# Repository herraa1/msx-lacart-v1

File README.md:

# MSX LOGICAL ANALYZER CART

This is a MSX cartridge to facilitate the use of a Logical Analyzer with MSX cartridges and slot signals.

It uses [Agustín Gimenez Bernad](https://github.com/gusmanb) Raspberry Pico 2 based [logicanalizer](https://github.com/gusmanb/logicanalyzer) as a companion card.

## Current Status

* First prototype PCB sent for manufacturing as of Apr 3rd 2026.
* First prototype PCB tested successfully as of Apr 18th 2026.

> [!NOTE]
> Documentation in progress

## [Hardware](hardware/kicad/)

The msx-lacart is made of a 4-layer PCB with minimal components.

### [msx-lacart-v1-build1](hardware/kicad/msx-lacart-v1-build1/)

:white_check_mark: This board has been successfully built and tested.

[Bill Of Materials (BoM)](https://htmlpreview.github.io/?https://raw.githubusercontent.com/herraa1/msx-lacart-v1/main/hardware/kicad/msx-lacart-v1-build1/bom/ibom.html)

[Schematic and PCB](https://kicanvas.org/?github=https%3A%2F%2Fgithub.com%2Fherraa1%2Fmsx-lacart-v1%2Ftree%2Fmain%2Fhardware%2Fkicad%2Fmsx-lacart-v1-build1)

|||
|-|-|
|msx-lacart-v1 build1<br>PCB unpopulated front|msx-lacart-v1 build1<br>PCB unpopulated back|

||
|:--|
|msx-lacart-v1 build1 PCB populated front|

||
|:--|
|msx-lacart-v1 build1 PCB populated back|

## Usage

||
|:--|
|msx-lacart-v1 inserted into slot1 of a MSX JFF inspecting a Knighmare cartridge|

||
|:--|
|msx-lacart-v1 with Logic Analyzer capture session|

```
                    di                                      ;[0000] f3
                    jp        $02d7                         ;[0001] c3 d7 02
[...]
                    ld        a,$82                         ;[02d7] 3e 82
                    out       ($ab),a                       ;[02d9] d3 ab
                    xor       a                             ;[02db] af
                    out       ($a8),a                       ;[02dc] d3 a8
                    ld        a,$50                         ;[02de] 3e 50
                    out       ($aa),a                       ;[02e0] d3 aa
                    ld        de,$ffff                      ;[02e2] 11 ff ff
                    xor       a                             ;[02e5] af
                    ld        c,a                           ;[02e6] 4f
                    out       ($a8),a                       ;[02e7] d3 a8
                    sla       c                             ;[02e9] cb 21
                    ld        b,$00                         ;[02eb] 06 00
                    ld        hl,$ffff                      ;[02ed] 21 ff ff
                    ld        (hl),$f0                      ;[02f0] 36 f0
                    ld        a,(hl)                        ;[02f2] 7e
                    sub       $0f                           ;[02f3] d6 0f
                    jr        nz,$0302                      ;[02f5] 20 0b
[...]
                    ld        hl,$bf00                      ;[0302] 21 00 bf
                    ld        a,(hl)                        ;[0305] 7e
                    cpl                                     ;[0306] 2f
                    ld        (hl),a                        ;[0307] 77
```
||
|:--|
|Original MSX BIOS Z80 instructions from BIOS disassembly|

||
|:--|
|El Dr Gusman Logic Analyzer 6.5 showing MSX BIOS Z80 boot instructions captured using msx-lacart-v1|

||
|:--|
|PulseView loaded with CSV export of MSX BIOS Z80 boot instructions captured using msx-lacart-v1|

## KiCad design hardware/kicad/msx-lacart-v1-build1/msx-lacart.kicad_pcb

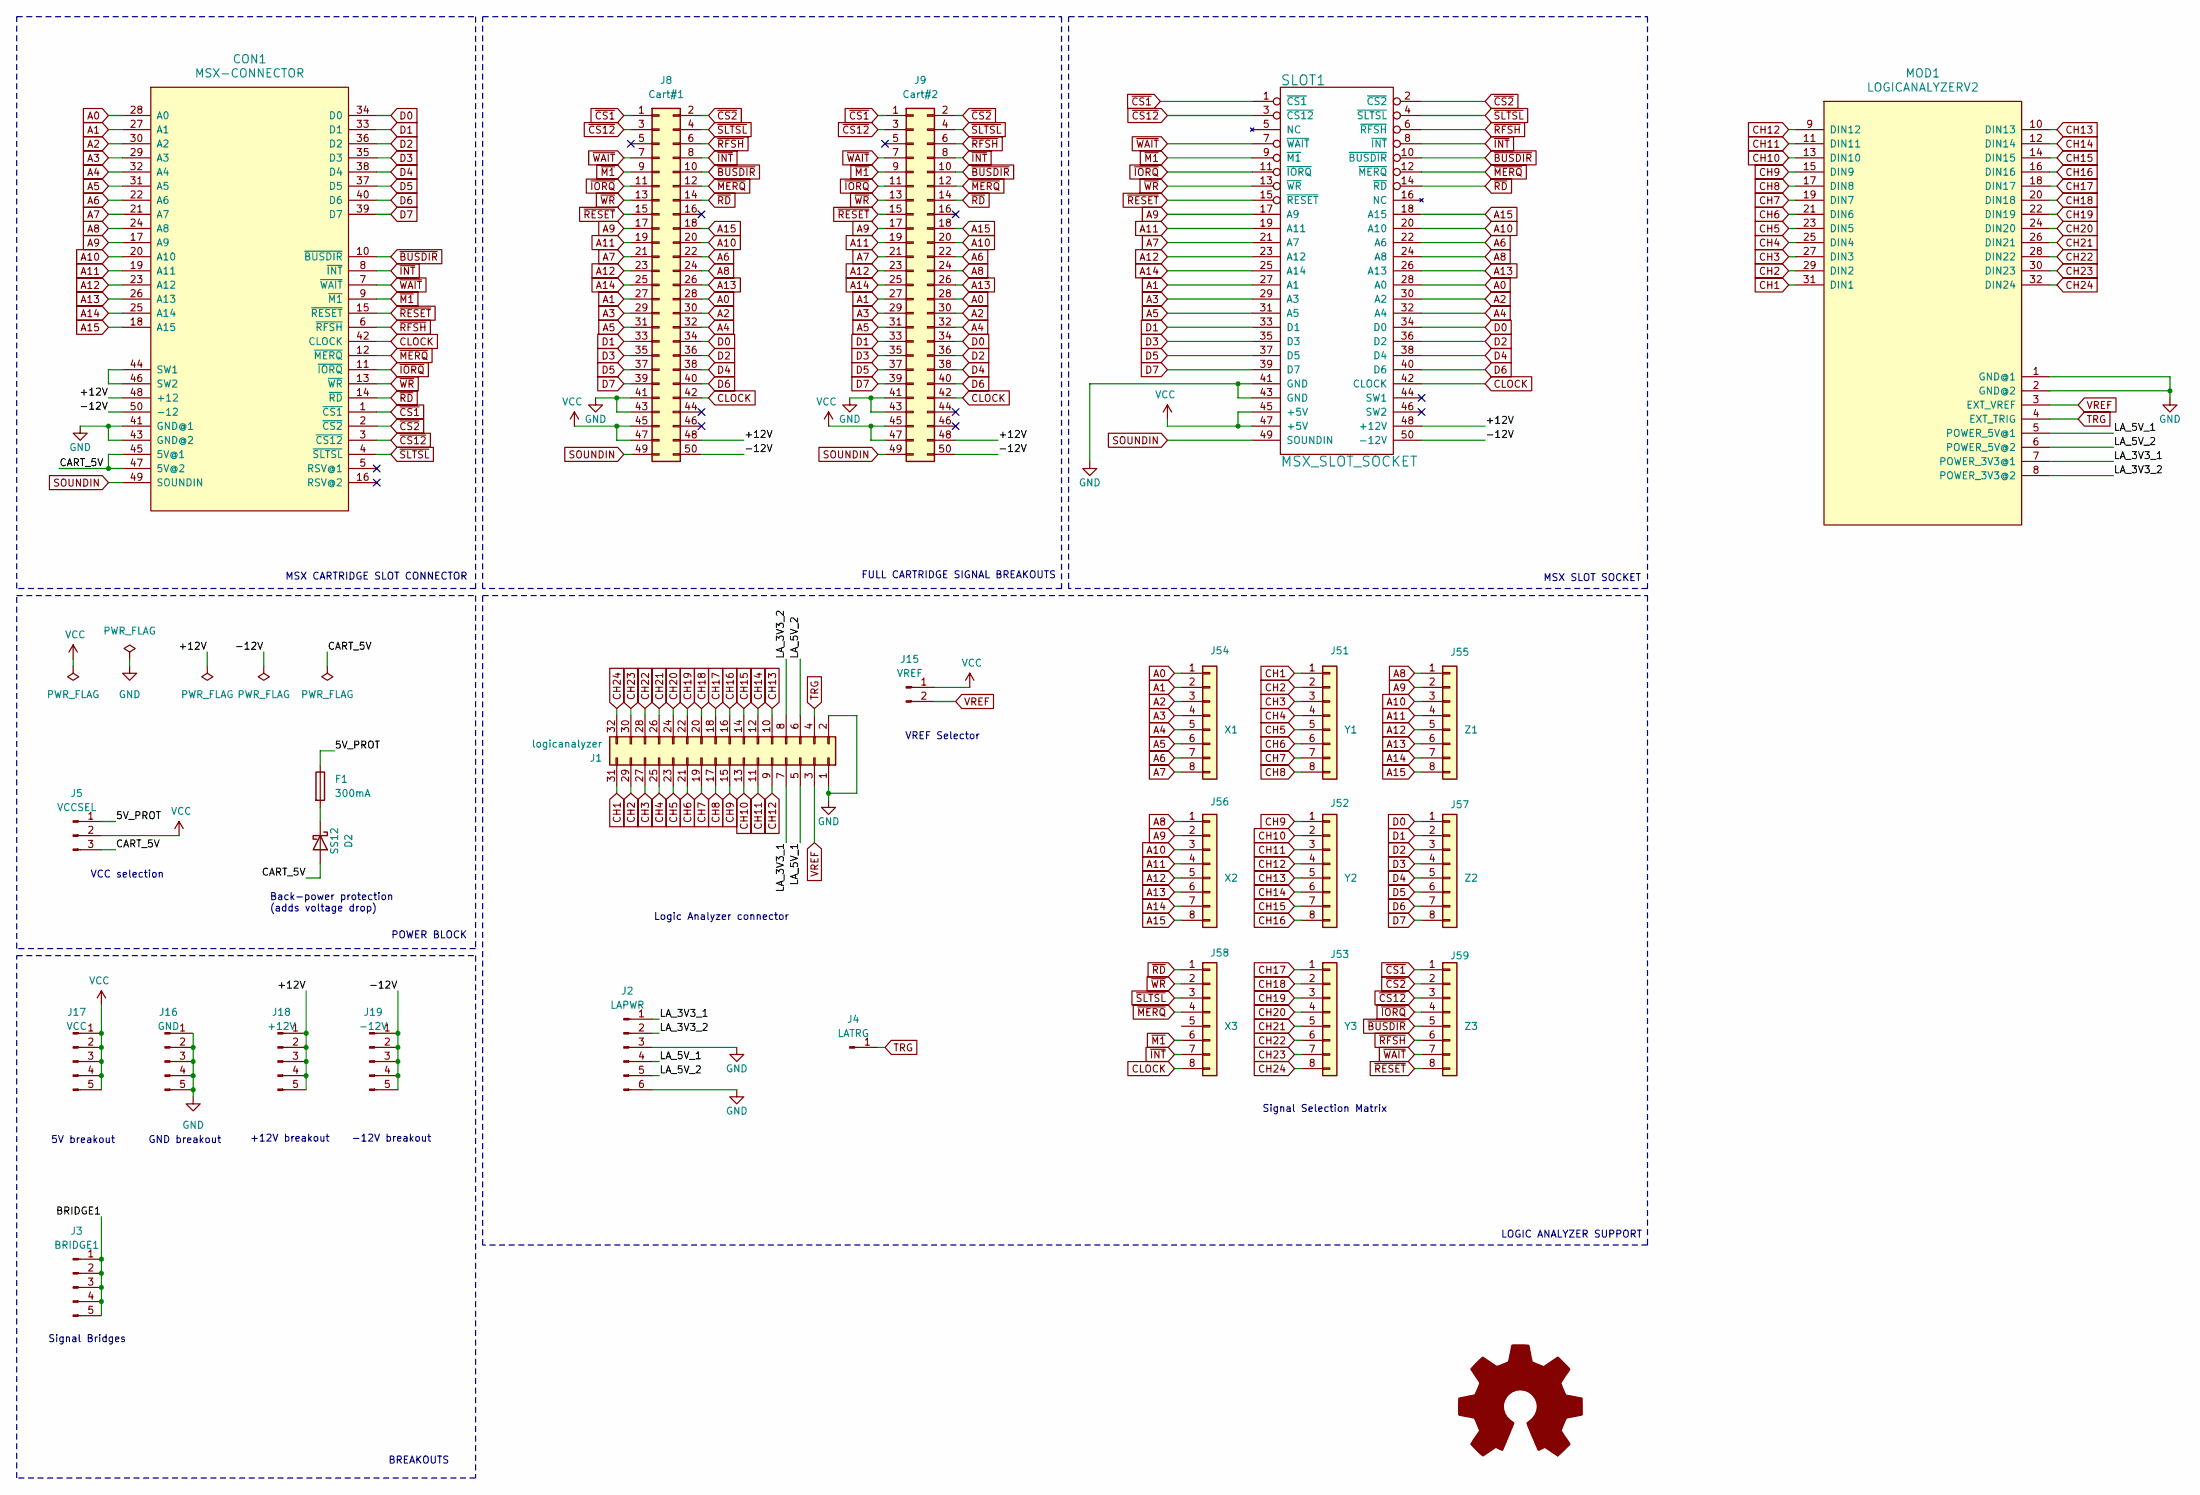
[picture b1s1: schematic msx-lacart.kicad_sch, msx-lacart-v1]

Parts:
CON1: MSX-CONNECTOR; CARTRIDGE_MSX_NOCUT
D2: SS12; D_SMA-SMB_Universal_Handsoldering
F1: 300mA; Fuse_1206_3216Metric_Pad1.42x1.75mm_HandSolder
J1: logicanalyzer; PinSocket_2x16_P2.54mm_Horizontal
J2: LAPWR; PinHeader_1x06_P2.54mm_Vertical
J3: BRIDGE1; PinHeader_1x05_P2.54mm_Vertical
J4: LATRG; PinHeader_1x01_P2.54mm_Vertical
J5: VCCSEL; PinHeader_1x03_P2.54mm_Vertical
J8: Cart#1; PinHeader_2x25_P2.54mm_Vertical
J9: Cart#2; PinHeader_2x25_P2.54mm_Vertical
J15: VREF; PinHeader_1x02_P2.54mm_Vertical
J16: GND; PinHeader_1x05_P2.54mm_Vertical
J17: VCC; PinHeader_1x05_P2.54mm_Vertical
J18: +12V; PinHeader_1x05_P2.54mm_Vertical
J19: -12V; PinHeader_1x05_P2.54mm_Vertical
J51: Y1; PinHeaderCustom_1x08_P2.54mm_Vertical
J52: Y2; PinHeaderCustom_1x08_P2.54mm_Vertical
J53: Y3; PinHeaderCustom_1x08_P2.54mm_Vertical
J54: X1; PinHeaderCustom_1x08_P2.54mm_Vertical
J55: Z1; PinHeaderCustom_1x08_P2.54mm_Vertical
J56: X2; PinHeaderCustom_1x08_P2.54mm_Vertical
J57: Z2; PinHeaderCustom_1x08_P2.54mm_Vertical
J58: X3; PinHeaderCustom_1x08_P2.54mm_Vertical
J59: Z3; PinHeaderCustom_1x08_P2.54mm_Vertical
MOD1: LOGICANALYZERV2; LogicAnalyzerV2
SLOT1: MSX_SLOT_SOCKET; Conn_Edge_50P
SYM1: Logo_Open_Hardware_Large; OSHW-Logo_7.5x8mm_SilkScreen

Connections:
/5V_PROT: F1.1, J5.1
/+12V: CON1.48 (+12), J8.48, J9.48, J18.1, J18.2, J18.3, J18.4, J18.5, SLOT1.48 (+12V)
/-12V: CON1.50 (-12), J8.50, J9.50, J19.1, J19.2, J19.3, J19.4, J19.5, SLOT1.50 (-12V)
/BRIDGE1: J3.1, J3.2, J3.3, J3.4, J3.5
/CART_5V: CON1.45 (5V@1), CON1.47 (5V@2), D2.2 (A), J5.3
/LA_3V3_1: J1.7, J2.1, MOD1.7 (POWER_3V3@1)
/LA_3V3_2: J1.8, J2.2, MOD1.8 (POWER_3V3@2)
/LA_5V_1: J1.5, J2.4, MOD1.5 (POWER_5V@1)
/LA_5V_2: J1.6, J2.5, MOD1.6 (POWER_5V@2)
A0: CON1.28 (A0), J8.28, J9.28, J54.1, SLOT1.28 (A0)
A1: CON1.27 (A1), J8.27, J9.27, J54.2, SLOT1.27 (A1)
A2: CON1.30 (A2), J8.30, J9.30, J54.3, SLOT1.30 (A2)
A3: CON1.29 (A3), J8.29, J9.29, J54.4, SLOT1.29 (A3)
A4: CON1.32 (A4), J8.32, J9.32, J54.5, SLOT1.32 (A4)
A5: CON1.31 (A5), J8.31, J9.31, J54.6, SLOT1.31 (A5)
A6: CON1.22 (A6), J8.22, J9.22, J54.7, SLOT1.22 (A6)
A7: CON1.21 (A7), J8.21, J9.21, J54.8, SLOT1.21 (A7)
A8: CON1.24 (A8), J8.24, J9.24, J55.1, J56.1, SLOT1.24 (A8)
A9: CON1.17 (A9), J8.17, J9.17, J55.2, J56.2, SLOT1.17 (A9)
A10: CON1.20 (A10), J8.20, J9.20, J55.3, J56.3, SLOT1.20 (A10)
A11: CON1.19 (A11), J8.19, J9.19, J55.4, J56.4, SLOT1.19 (A11)
A12: CON1.23 (A12), J8.23, J9.23, J55.5, J56.5, SLOT1.23 (A12)
A13: CON1.26 (A13), J8.26, J9.26, J55.6, J56.6, SLOT1.26 (A13)
A14: CON1.25 (A14), J8.25, J9.25, J55.7, J56.7, SLOT1.25 (A14)
A15: CON1.18 (A15), J8.18, J9.18, J55.8, J56.8, SLOT1.18 (A15)
CH1: J1.31, J51.1, MOD1.31 (DIN1)
CH2: J1.29, J51.2, MOD1.29 (DIN2)
CH3: J1.27, J51.3, MOD1.27 (DIN3)
CH4: J1.25, J51.4, MOD1.25 (DIN4)
CH5: J1.23, J51.5, MOD1.23 (DIN5)
CH6: J1.21, J51.6, MOD1.21 (DIN6)
CH7: J1.19, J51.7, MOD1.19 (DIN7)
CH8: J1.17, J51.8, MOD1.17 (DIN8)
CH9: J1.15, J52.1, MOD1.15 (DIN9)
CH10: J1.13, J52.2, MOD1.13 (DIN10)
CH11: J1.11, J52.3, MOD1.11 (DIN11)
CH12: J1.9, J52.4, MOD1.9 (DIN12)
CH13: J1.10, J52.5, MOD1.10 (DIN13)
CH14: J1.12, J52.6, MOD1.12 (DIN14)
CH15: J1.14, J52.7, MOD1.14 (DIN15)
CH16: J1.16, J52.8, MOD1.16 (DIN16)
CH17: J1.18, J53.1, MOD1.18 (DIN17)
CH18: J1.20, J53.2, MOD1.20 (DIN18)
CH19: J1.22, J53.3, MOD1.22 (DIN19)
CH20: J1.24, J53.4, MOD1.24 (DIN20)
CH21: J1.26, J53.5, MOD1.26 (DIN21)
CH22: J1.28, J53.6, MOD1.28 (DIN22)
CH23: J1.30, J53.7, MOD1.30 (DIN23)
CH24: J1.32, J53.8, MOD1.32 (DIN24)
CLOCK: CON1.42 (CLOCK), J8.42, J9.42, J58.8, SLOT1.42 (CLOCK)
D0: CON1.34 (D0), J8.34, J9.34, J57.1, SLOT1.34 (D0)
D1: CON1.33 (D1), J8.33, J9.33, J57.2, SLOT1.33 (D1)
D2: CON1.36 (D2), J8.36, J9.36, J57.3, SLOT1.36 (D2~)
D3: CON1.35 (D3), J8.35, J9.35, J57.4, SLOT1.35 (D3)
D4: CON1.38 (D4), J8.38, J9.38, J57.5, SLOT1.38 (D4)
D5: CON1.37 (D5), J8.37, J9.37, J57.6, SLOT1.37 (D5)
D6: CON1.40 (D6), J8.40, J9.40, J57.7, SLOT1.40 (D6)
D7: CON1.39 (D7), J8.39, J9.39, J57.8, SLOT1.39 (D7)
GND: CON1.41 (GND@1), CON1.43 (GND@2), J1.1, J1.2, J2.3, J2.6, J8.41, J8.43, J9.41, J9.43, J16.1, J16.2, J16.3, J16.4, J16.5, MOD1.1 (GND@1), MOD1.2 (GND@2), SLOT1.41 (GND), SLOT1.43 (GND)
unnamed: CON1.44 (SW1), CON1.46 (SW2)
unnamed: D2.1 (K), F1.2
SOUNDIN: CON1.49 (SOUNDIN), J8.49, J9.49, SLOT1.49 (SOUNDIN)
TRG: J1.4, J4.1, MOD1.4 (EXT_TRIG)
VCC: J5.2, J8.45, J8.47, J9.45, J9.47, J15.1, J17.1, J17.2, J17.3, J17.4, J17.5, SLOT1.45 (+5V), SLOT1.47 (+5V)
VREF: J1.3, J15.2, MOD1.3 (EXT_VREF)
~BUSDIR: CON1.10 (~BUSDIR), J8.10, J9.10, J59.5, SLOT1.10 (~BUSDIR)
~CS1: CON1.1 (~CS1), J8.1, J9.1, J59.1, SLOT1.1 (~CS1)
~CS2: CON1.2 (~CS2), J8.2, J9.2, J59.2, SLOT1.2 (~CS2)
~CS12: CON1.3 (~CS12), J8.3, J9.3, J59.3, SLOT1.3 (~CS12)
~INT: CON1.8 (~INT), J8.8, J9.8, J58.7, SLOT1.8 (~INT)
~IORQ: CON1.11 (~IORQ), J8.11, J9.11, J59.4, SLOT1.11 (~IORQ)
~M1: CON1.9 (~M1), J8.9, J9.9, J58.6, SLOT1.9 (~M1)
~MERQ: CON1.12 (~MERQ), J8.12, J9.12, J58.4, SLOT1.12 (~MERQ)
~RD: CON1.14 (~RD), J8.14, J9.14, J58.1, SLOT1.14 (~RD)
~RESET: CON1.15 (~RESET), J8.15, J9.15, J59.8, SLOT1.15 (~RESET)
~RFSH: CON1.6 (~RFSH), J8.6, J9.6, J59.6, SLOT1.6 (~RFSH)
~SLTSL: CON1.4 (~SLTSL), J8.4, J9.4, J58.3, SLOT1.4 (~SLTSL)
~WAIT: CON1.7 (~WAIT), J8.7, J9.7, J59.7, SLOT1.7 (~WAIT)
~WR: CON1.13 (~WR), J8.13, J9.13, J58.2, SLOT1.13 (~WR)

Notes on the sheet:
5V breakout
Back-power protection (adds voltage drop)
MSX SLOT SOCKET
-12V breakout
MSX CARTRIDGE SLOT CONNECTOR
Logic Analyzer connector
+12V breakout
Signal Selection Matrix
GND breakout
POWER BLOCK
LOGIC ANALYZER SUPPORT
FULL CARTRIDGE SIGNAL BREAKOUTS
Signal Bridges
BREAKOUTS
VREF Selector
VCC selection

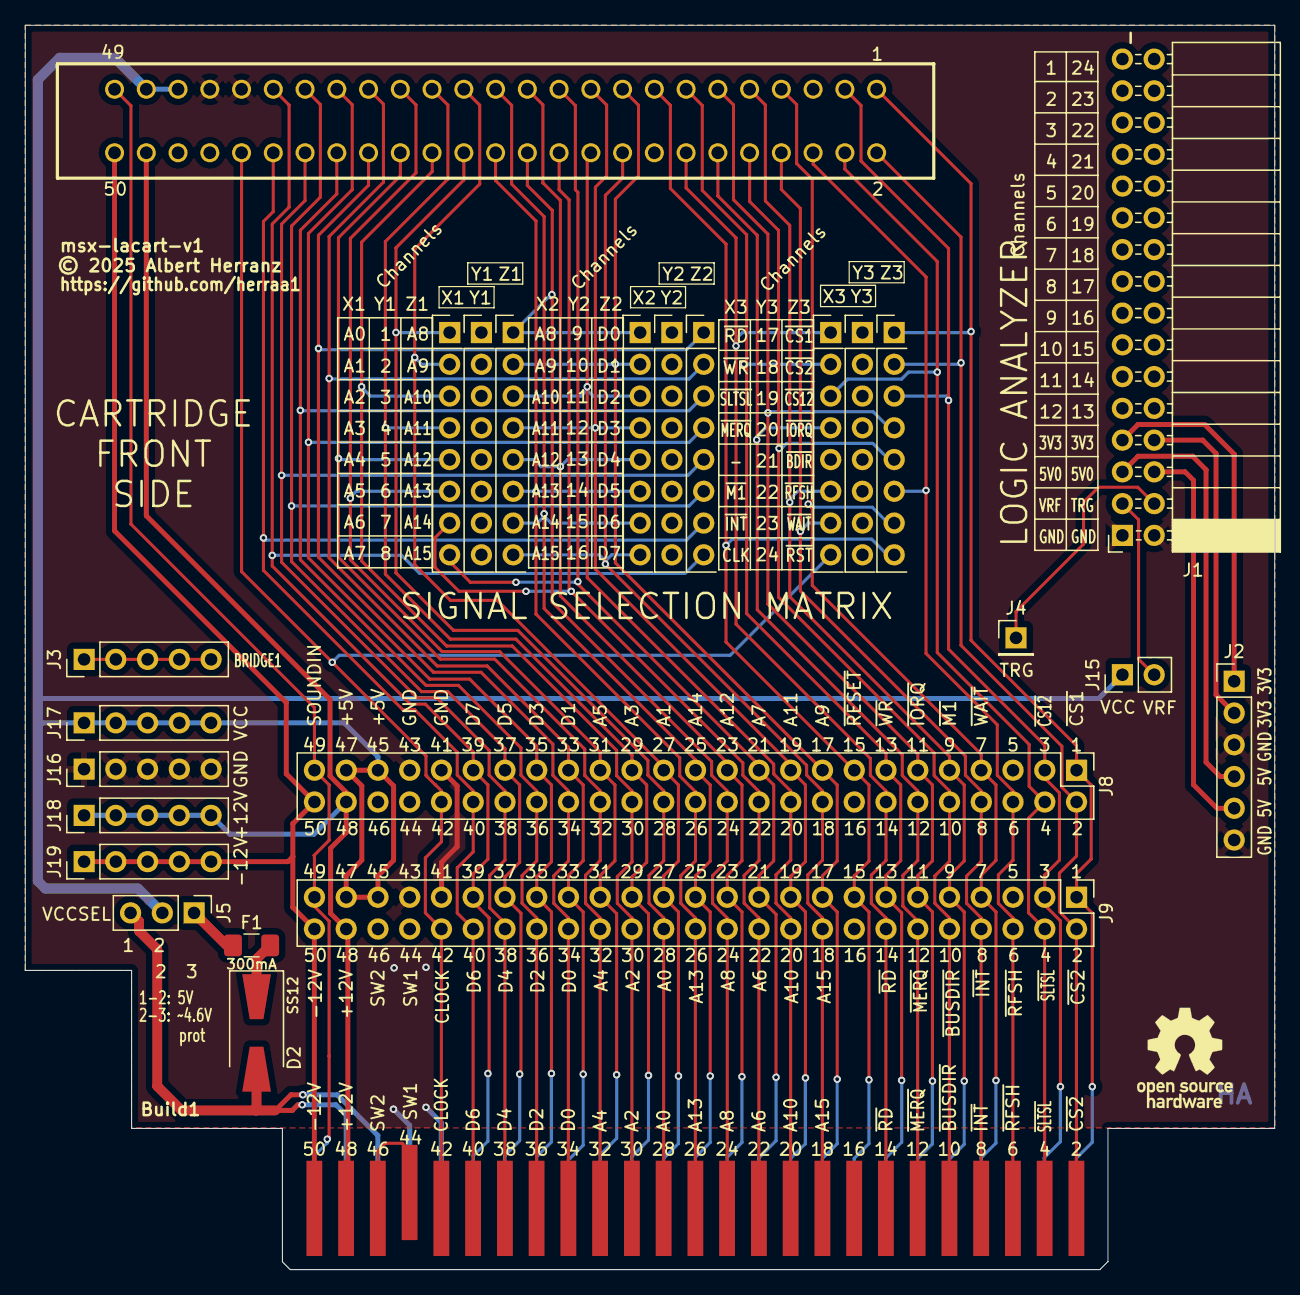
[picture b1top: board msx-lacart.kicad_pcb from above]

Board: 4 copper layers, 99.9 x 99.5 mm, 26 parts (0 on the bottom side), 79 nets.

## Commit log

2026-04-19 Initial commit.
2026-04-19 readme: fix incorrect link
2026-04-20 readme: small redaction

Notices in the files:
hardware/kicad/msx-lacart-v1-build1/msx-lacart.kicad_pcb:
© 2025 Albert Herranz
